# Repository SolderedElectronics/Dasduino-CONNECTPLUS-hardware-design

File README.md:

# Dasduino CONNECTPLUS Hardware Design

## About the Product

|  |
| :----------------------------------------------------------: |
| [Buy Dasduino CONNECTPLUS](https://www.solde.red/333033) |

If you’re looking for a microcontroller simple-to-use, yet powerful enough for a wide variety of applications, look no further from our connectplus. From low-power sensor networks to demanding tasks such as streaming music, MP3 encoding, and voice recording, this microcontroller can do it all. Dasduino CONNECTPLUS comes with integrated Wi-Fi and Bluetooth 4.2, which enable low-energy secure connections with data packet length extensions. It uses the powerful ESP32 controller with 4 MB integrated flash and 8 MB integrated PSRAM.

Dasduino CONNECTPLUS is 69 mm wide and 26 mm high. It fits on a standard breadboard for faster prototyping and works for most projects. It offers plenty of external connections with its 30 pins.You can simply connect the board to your computer with the standard USB Type-C cable and program it with Arduino IDE. The qwiic port lets you connect the CONNECTPLUS easily with other I2C devices. The JST battery connector and onboard charger lets you make your projects truly wireless. There is more: full RGB WS2812 LED, reset and user button, onboard protections and more. It comes with USB-C cable.

---

## Repository Contents

This repository contains all design files for Dasduino CONNECTPLUS, organized as follows:

- **`CAD` folder**: Contains KiCAD design files, including:
  - Schematics
  - PCB layout
  - Panel PCB layout
  - Source 3D files in Fusion360, if any
  - All files are sorted by version with a detailed change log.
- **`OUTPUTS` folder**: Includes all production-ready files, such as:
  - Bill of Materials (BOM) and interactive BOM (iBOM)
  - PDF versions of schematics
  - 3D `.step` file of the board
  - 3D-printable models
  - Gerber files for PCB manufacturing
  - Image of the pinout of the board
  - Product image
  - Compliance, legal and generic sales documents

Refer to the `Change Log` in the CAD folder for details about updates between versions.

---

## Learn More About the Product

Beyond the repository, explore the following resources:

### Soldered Verify

The **Soldered Verify** system ensures every board you purchase from Soldered is fully functional. It also provides access to exclusive test data for your product. To get started, find the unique Soldered Verify ID on your product's packaging and enter the ID on the [Soldered Verify page](https://soldered.com/verify/) to access test results and additional product details.

### Soldered Community

Soldered Community is your go-to place for technical support. Our engineers track and answer all questions posted there, and it’s a great space for the maker community. Get answers to your questions and solutions for your challenges at [Soldered Community](https://soldered.com/community).

### solde.red

solde.red is an ultimate URL shortener and information hub. Access it by typing solde.red/ followed by your product SKU, e.g., [solde.red/333000](https://solde.red/333000), to find getting-started guides, datasheets, open-source hardware and software files, certifications, images, pinouts, and more. Read more about the shortener [here](https://solde.red/info/).

---

## Contributing

Contributions are welcome! Here’s how you can get involved:

- Submit pull requests to enhance the design or fix issues.
- Report bugs or problems by opening an issue.

We encourage community collaboration to make this product even better.

---

## About Soldered

[Soldered for Makers](https://soldered.com) specializes in designing and manufacturing electronic products tailored for enthusiasts, ranging from hobbyists to professionals. Our portfolio includes electronic boards, sensors, and actuators that are widely utilized in fields such as microelectronics, mechatronics, robotics, programming, and IoT. Every product we offer is designed in-house and built upon open-source hardware and software platforms. Proudly certified and manufactured within the European Union, our catalog likely includes the product you need for your project.

We complement these products with comprehensive tutorials and manuals, product descriptions, schematics, programming codes, and project examples. Our round-the-clock [customer and technical support](https://soldered.com/community) is available for all our products, irrespective of the sales channel. Soldered’s success and services reflect our maker community’s unwavering [trust](https://www.trustpilot.com/review/soldered.com), for which we are deeply grateful. Join our community and create using Soldered products.

---

## License

All Soldered open-source hardware (OSH) is under The TAPR Open Hardware License. Read more in the LICENSE file located in this repository.

**Disclaimer:**

No warranty - all designs in this repository are distributed in the hope that they will be useful, but without any warranty. They are provided "AS IS", therefore without warranty of any kind, either expressed or implied. The entire quality and performance of what you do with the contents of this repository are your responsibility. In no event Soldered Electronics will be liable for your damages, or losses, including any general, special, incidental, or consequential damage arising out of the use or inability to use the contents of this repository. 

---

## Have fun!

Thank you for your support from your fellow makers at Soldered Electronics.

Happy Making!

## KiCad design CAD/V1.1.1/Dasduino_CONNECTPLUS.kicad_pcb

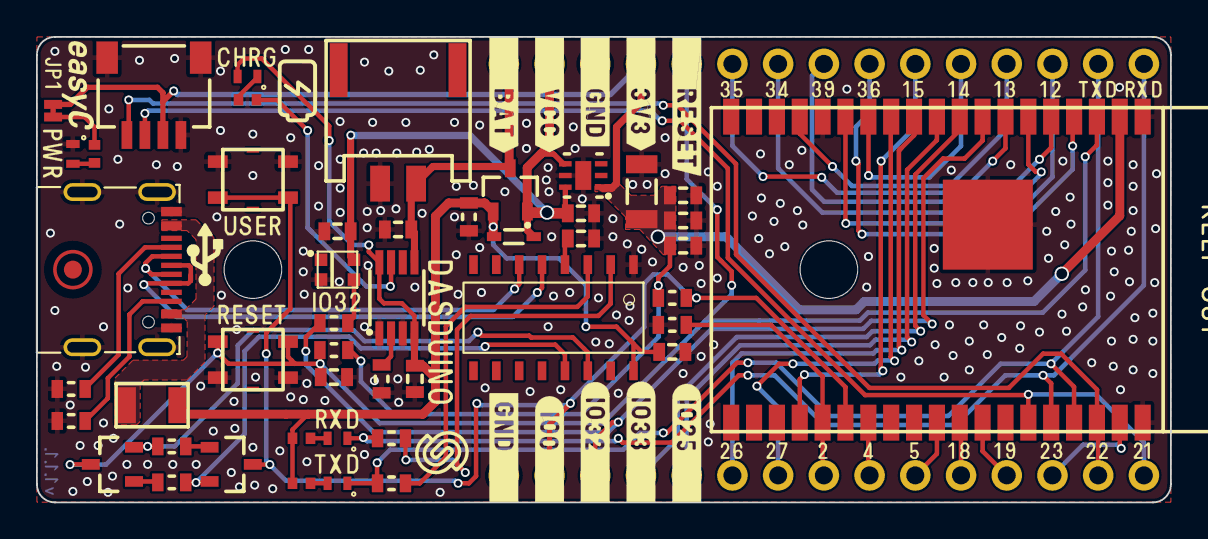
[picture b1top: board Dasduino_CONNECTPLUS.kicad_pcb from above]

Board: 2 copper layers, 63.0 x 25.9 mm, 52 parts (0 on the bottom side), 50 nets.

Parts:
C1: 10uF; 1206C
C2, C5: 1uF; 0603C
C3, C4, C6: 0.1uF; 0603C
C7, C8, C9, C10: 2.2uF; 0603C
C11: 100nF; 0603C
D1: white; 0402LED
D2: blue; 0402LED
D3: purple; 0402LED
D4: WS2812B-2020
D5: schottky diode; SOD-323
D6: red; 0402LED
F1: 1206FUSE-500mA; 1206FUSE
FD1: FIDUCIAL; FIDUCIAL_23
H1, H3: HOLE_3.2mm
JP1: SMD-JUMPER-CONNECTED_TRACE_SLODERMASK
K1: U262-161N-4BVC11
K2: easyC-SMD; easyC-connector
K3: JST-2pin-SMD
K4, K5: HEADER_MALE_15X1
Q1: PMOS-SOT-23-3; SOT-23-3
Q2, Q3: NPN-SOT-23-3; SOT-23-3
R1, R10, R11, R12, R13: 10k; 0603R
R2, R3: 5.1k; 0603R
R4, R5, R17: 1k; 0603R
R6, R7, R8, R15: 2k2; 0402R
R9: 100k; 0603R
R14: 3k; 0603R
SW1, SW2: YTSA007A0151803B
U1: CH340C; SOP-16
U2: ESP32-WROVER
U3: TPS7A2633DRVR
U4: TP4056M; TP4056M-MSOP8

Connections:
+3V3: C1.2, C5.2, C6.2, C8.2, JP1.1, K2.3 (3V3), K4.4, R1.2, R13.2, U2.2 (VDD33), U3.1 (OUT)
D+: K1.A6 (DP1), K1.B6 (DP2), U1.5 (UD+)
D-: K1.A7 (DN1), K1.B7 (DN2), U1.6 (UD-)
DTR: Q3.2 (E), R10.1, U1.13 (DTR#)
GND: C1.1, C2.1, C3.1, C4.2, C5.1, C6.1, C7.1, C8.1, C9.1, C10.1, C11.2, D3.2 (K), D4.2 (GND), K1.A1 (GND), K1.A12 (GND), K1.B1 (GND), K1.B12 (GND), K1.SH (SHIELD), K2.4 (GND), K2.5 (SHIELD), K3.2 (-), K4.3, K5.1, R2.2, R3.2, R9.1, R12.1, R14.2, SW1.2, SW2.1, U1.1 (GND), U2.1 (GND), U2.15 (GND), U2.38 (GND), U2.39 (GND), U3.5 (GND), U4.1 (TEMP), U4.3 (GND)
IO0: K5.2, Q3.3 (C), R13.1, SW2.2, U2.25 (IO0)
IO2: K5.8, R12.2, U2.24 (IO2)
IO4: K5.9, U2.26 (IO4)
IO5: K5.10, U2.29 (IO5)
IO18: K5.11, U2.30 (IO18)
IO19: K5.12, U2.31 (IO19)
IO23: K5.13, U2.37 (IO23)
IO25: K5.5, U2.10 (IO25)
IO26: K5.6, U2.11 (IO26)
IO27: K5.7, U2.12 (IO27)
IO32: K5.3, R17.1, U2.8 (IO32)
IO33: K5.4, U2.9 (IO33)
IO34: K4.7, U2.6 (IO34)
IO35: K4.6, U2.7 (IO35)
unnamed: C4.1, U1.4 (V3)
unnamed: D1.1 (A), R6.1
unnamed: D2.1 (A), R7.1
unnamed: D3.1 (A), R8.2
unnamed: D4.3 (DI), R17.2
unnamed: D6.2 (K), R15.2
unnamed: F1.2, K1.A4 (VBUS), K1.A9 (VBUS), K1.B4 (VBUS), K1.B9 (VBUS)
unnamed: K1.A5 (CC1), R3.1
unnamed: K1.B5 (CC2), R2.1
unnamed: Q2.1 (B), R10.2
unnamed: Q3.1 (B), R11.2
unnamed: R4.1, U1.2 (TXD)
unnamed: R5.1, U1.3 (RXD)
unnamed: JP1.2, R8.1
unnamed: R14.1, U4.2 (PROG)
unnamed: R15.1, U4.7 (~CHRG)
RESET: C2.2, K4.5, Q2.3 (C), R1.1, SW1.1, U2.3 (EN)
RTS: Q2.2 (E), R11.1, U1.14 (RTS#)
RXD0: D2.2 (K), K4.15, R4.2, U2.34 (RXD0)
SCL: K2.1 (SCL), K5.14, U2.36 (IO22)
SDA: K2.2 (SDA), K5.15, U2.33 (IO21)
SENSOR_VN: K4.8, U2.5 (SENSOR_VN)
SENSOR_VP: K4.9, U2.4 (SENSOR_VP)
SPI_CS: K4.10, U2.23 (IO15)
SPI_MISO: K4.13, U2.14 (IO12)
SPI_MOSI: K4.12, U2.16 (IO13)
SPI_SCK: K4.11, U2.13 (IO14)
TXD0: D1.2 (K), K4.14, R5.2, U2.35 (TXD0)
VBAT: C9.2, K3.1 (+), K4.1, Q1.3 (D), U4.5 (BAT)
VCC: C7.2, C11.1, D4.4 (VDD), D5.2 (K), K4.2, Q1.2 (S), U3.4 (EN), U3.6 (IN)
VUSB: C3.2, C10.2, D5.1 (A), D6.1 (A), F1.1, Q1.1 (G), R6.2, R7.2, R9.2, U1.16 (VCC), U4.4 (VCC), U4.8 (CE)

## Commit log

2022-08-06 Updating open source files.
